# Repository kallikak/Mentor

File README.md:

# Constructive Synthesis Mentor

A complete single board polyphonic synthesiser based on a Teensy 4.0 and Teensy Audio Shield. Called Mentor due to its focus as an instrument for learning subtractive synthesis. <a href="http://thewessens.net/synthbook/#constructive-synthesis">Constructive Synthesis</a> is the associated website covering the basics for learning subtractive synthesis.

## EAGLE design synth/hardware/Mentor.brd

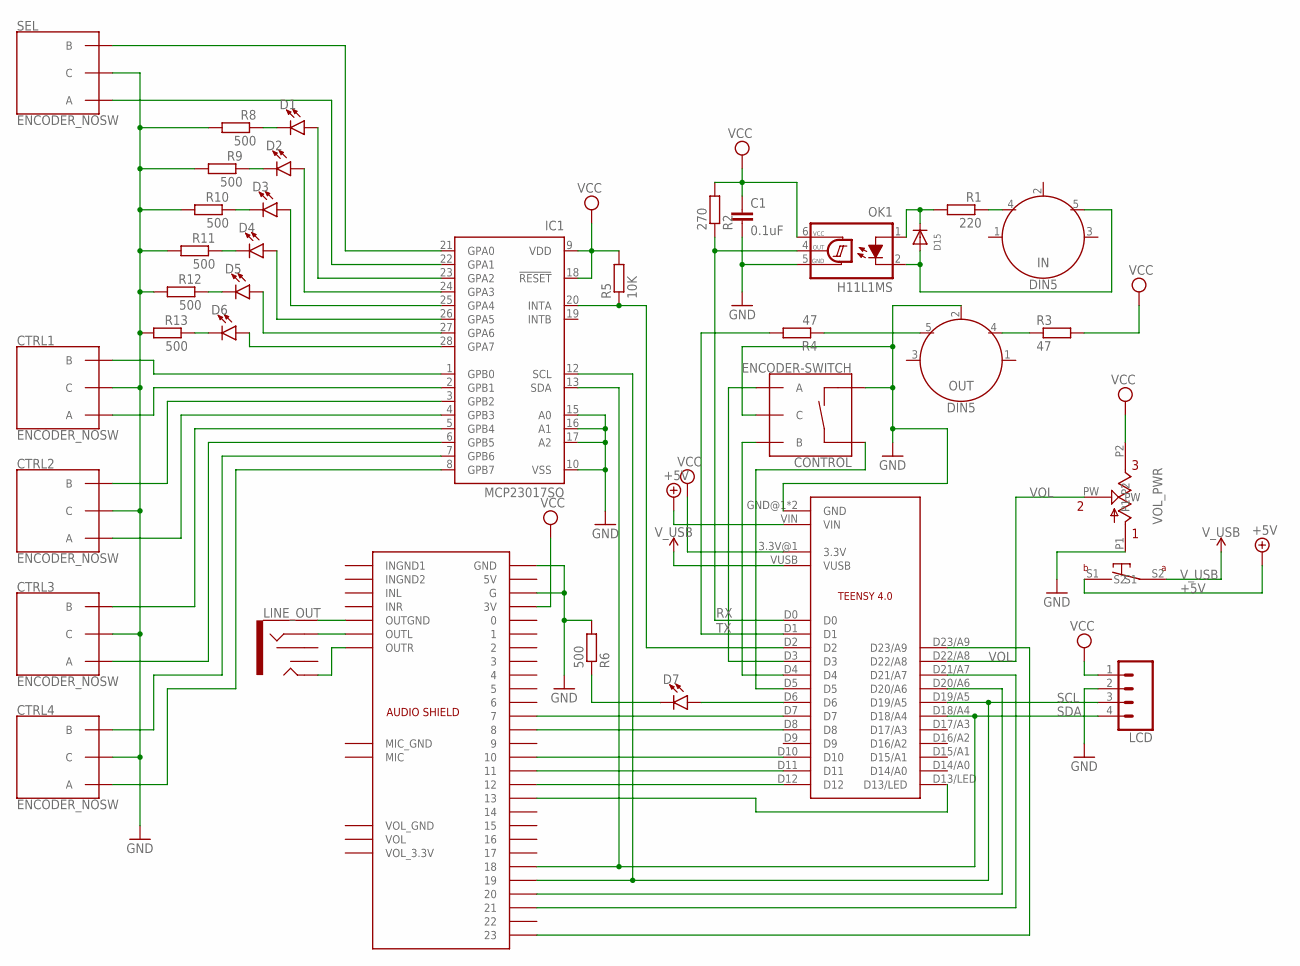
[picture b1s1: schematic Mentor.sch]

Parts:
C1: 0.1uF; C0603K
CONTROL: ENCODER-SWITCH; ROTARY_ENC_PLAIN
CTRL1, CTRL2, CTRL3, CTRL4: ENCODER_NOSW
D1, D2, D3, D4, D5, D6, D7: LED3MM; LED_3MM
D15: DIODESOD-123; SOD-123
IC1: MCP23017SO; SO28W
IN: DIN5; DIN5-RA-PTH
LCD: CONN_04LONGPADS; 1X04_LONGPADS
LINE_OUT: AUDIO_JACK_3.5MM_PTH; AUDIO-JACK
OK1: H11L1MS; DIL6-SMD
OUT: DIN5; DIN5-RA-PTH
R1: 220; R0603
R2: 270; R0603
R3, R4: 47; R0603
R5: 10K; R0603
R6, R8, R9, R10, R11, R12, R13: 500; R0603
SEL: ENCODER_NOSW
U$2: TEENSY4.0_SIMPLE
U$3: AUDIO SHIELD; AUDIOSHIELD
VOL_PWR: 10K; RK097-SINGLE-W/SWITCH

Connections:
+5V: U$2.VIN, VOL_PWR.S1
GND: C1.2, CONTROL.C, CONTROL.SW-, CTRL1.C, CTRL2.C, CTRL3.C, CTRL4.C, IC1.10 (VSS), IC1.15 (A0), IC1.16 (A1), IC1.17 (A2), LCD.2, OK1.5 (GND), OUT.2, R6.2, R8.2, R9.2, R10.2, R11.2, R12.2, R13.2, SEL.C, U$2.GND@1 (GND), U$2.GND@2 (GND), U$3.G, U$3.GND, VOL_PWR.P1
MISO: U$2.D12, U$3.12
MOSI: U$2.D11, U$3.11
unnamed: IC1.21 (GPA0), SEL.B
unnamed: IC1.22 (GPA1), SEL.A
unnamed: CTRL1.B, IC1.1 (GPB0)
unnamed: CTRL1.A, IC1.2 (GPB1)
unnamed: CTRL2.B, IC1.3 (GPB2)
unnamed: CTRL2.A, IC1.4 (GPB3)
unnamed: CTRL3.B, IC1.5 (GPB4)
unnamed: CTRL3.A, IC1.6 (GPB5)
unnamed: CTRL4.B, IC1.7 (GPB6)
unnamed: CTRL4.A, IC1.8 (GPB7)
unnamed: OUT.5, R4.1
unnamed: U$2.D20/A6, U$3.20
unnamed: U$2.D21/A7, U$3.21
unnamed: U$2.D23/A9, U$3.23
unnamed: U$2.D10, U$3.10
unnamed: U$2.D7, U$3.7
unnamed: U$2.D8, U$3.8
unnamed: IC1.20 (INTA), R5.1, U$2.D2
unnamed: D6.K (C), R13.1
unnamed: D1.K (C), R8.1
unnamed: D6.A, IC1.28 (GPA7)
unnamed: D7.K (C), R6.1
unnamed: D7.A, U$2.D6
unnamed: D2.K (C), R9.1
unnamed: D3.K (C), R10.1
unnamed: D3.A, IC1.25 (GPA4)
unnamed: CONTROL.A, U$2.D3
unnamed: CONTROL.B, U$2.D4
unnamed: CONTROL.SW+, U$2.D5
unnamed: D4.K (C), R11.1
unnamed: D5.K (C), R12.1
unnamed: D15.A, IN.5, OK1.2 (C)
unnamed: D15.C, OK1.1 (A), R1.2
unnamed: IN.4, R1.1
unnamed: LINE_OUT.SLEEVE, U$3.OUTGND
unnamed: OUT.4, R3.1
unnamed: LINE_OUT.RING, U$3.OUTL
unnamed: LINE_OUT.TIP, U$3.OUTR
RX: OK1.4 (OUT), R2.1, U$2.D0
SCK: U$2.D13/LED, U$3.13
SCL: IC1.12 (SCL), LCD.3, U$2.D19/A5, U$3.19
SDA: IC1.13 (SDA), LCD.4, U$2.D18/A4, U$3.18
SEL1: D1.A, IC1.23 (GPA2)
SEL2: D2.A, IC1.24 (GPA3)
SEL4: D4.A, IC1.26 (GPA5)
SEL5: D5.A, IC1.27 (GPA6)
TX: R4.2, U$2.D1
VCC: C1.1, IC1.9 (VDD), IC1.18 (!RESET), LCD.1, OK1.6 (VCC), R2.2, R3.2, R5.2, U$2.3.3V@1 (3.3V), U$3.3V, VOL_PWR.P2
VOL: U$2.D22/A8, VOL_PWR.PW
V_USB: U$2.VUSB, VOL_PWR.S2

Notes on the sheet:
AUDIO SHIELD

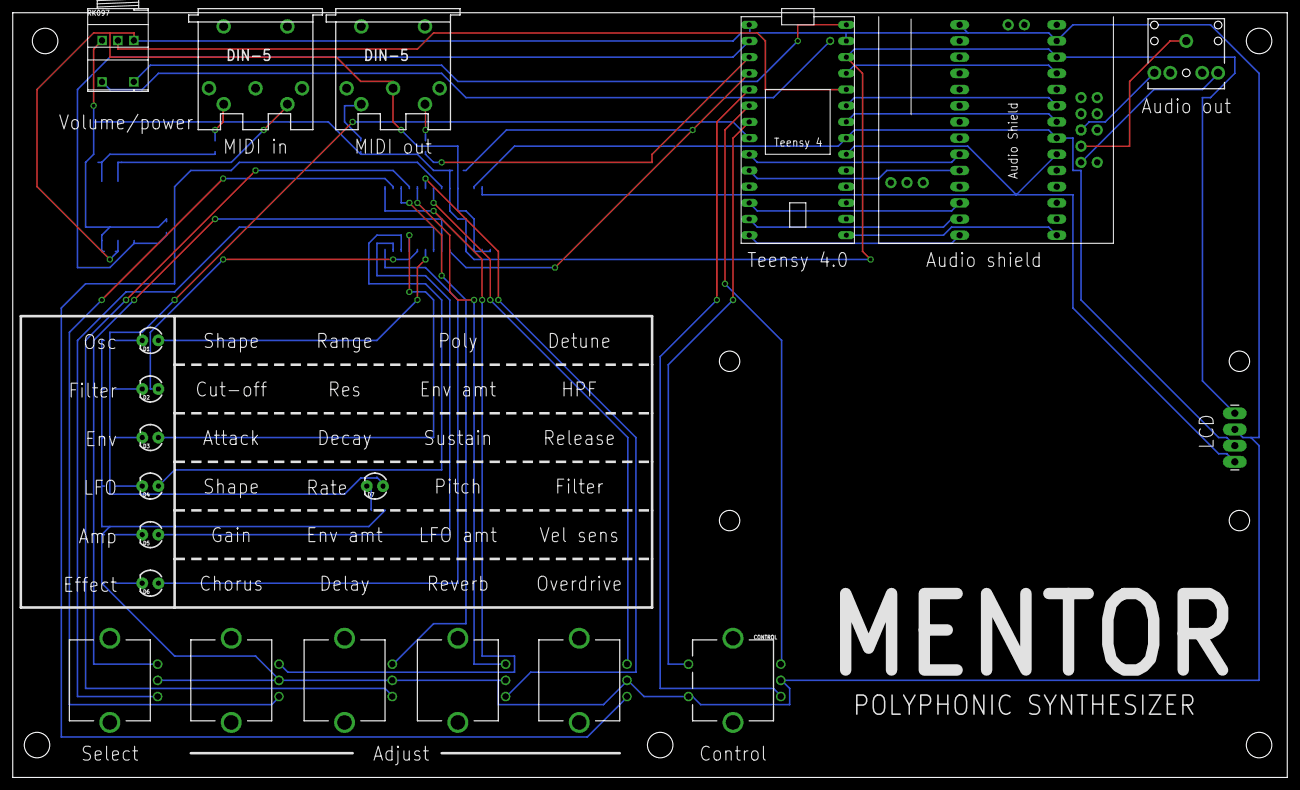
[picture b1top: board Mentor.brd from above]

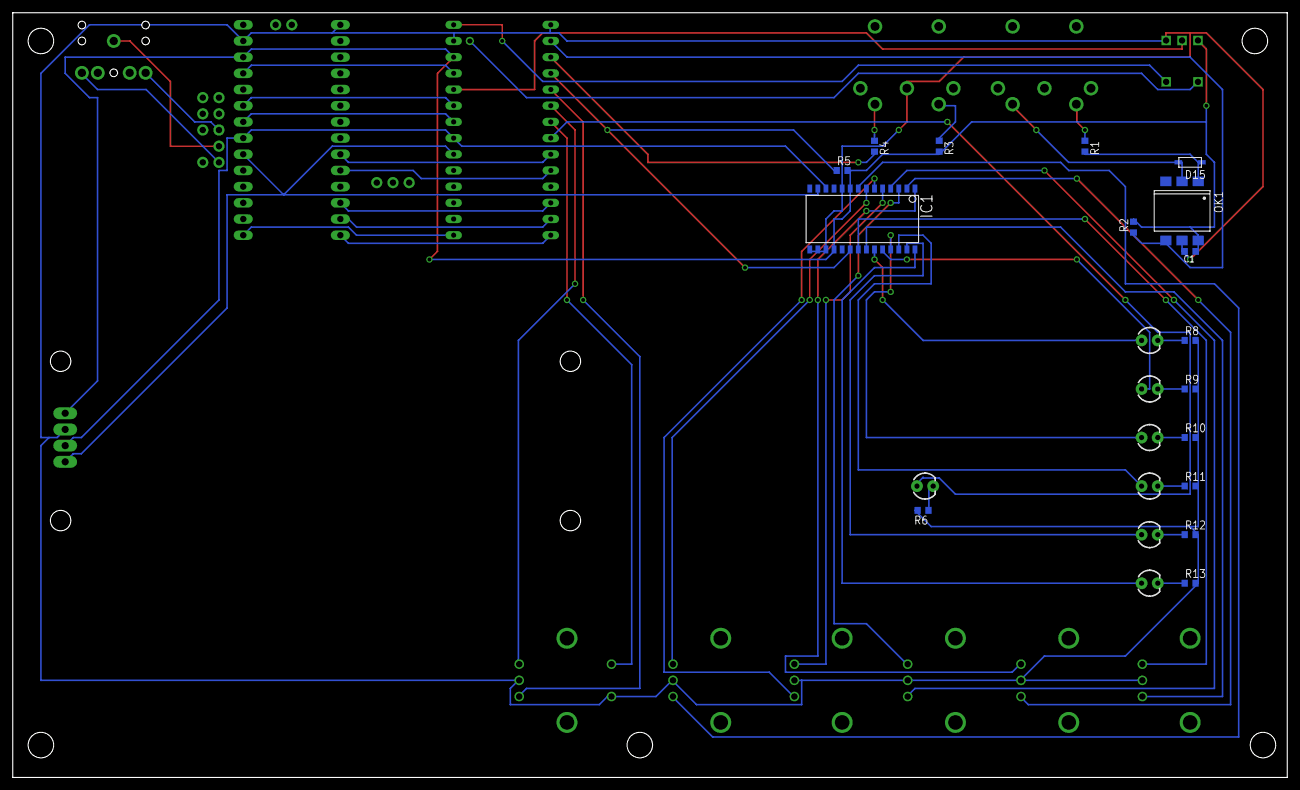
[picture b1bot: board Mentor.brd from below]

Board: 2 copper layers, 200.0 x 120.0 mm, 36 parts (16 on the bottom side), 54 nets.

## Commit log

2021-04-07 Create LICENSE
2021-04-29 Ready for draft-2
2021-05-01 Complete draft
2021-05-06 Minor bug fixes and improvements
2021-05-10 Various improvements + portamento
2022-06-24 Update - tests and wavefolding

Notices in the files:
parts and their libraries:
SparkFun-Switches: Licensing: Creative Commons ShareAlike 4.0 International - https://creativecommons.org/licenses/by-sa/4.0
